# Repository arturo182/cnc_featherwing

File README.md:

# CNC FeatherWing

Inspired by the Arduino CNC Shield, offers similar functionality. 

Requires a Feather-compatible board.

- 4 slots for Pololu stepper motor drivers, 3 axis + 1 clone axis (configurable via jumpers)
- Endstops for X/Y/Z with selectable active level (high or low)
- Pins for external buttons including emergency stop
- Pins for spindle and collant control
- Configurable microstep resolution via jumpers

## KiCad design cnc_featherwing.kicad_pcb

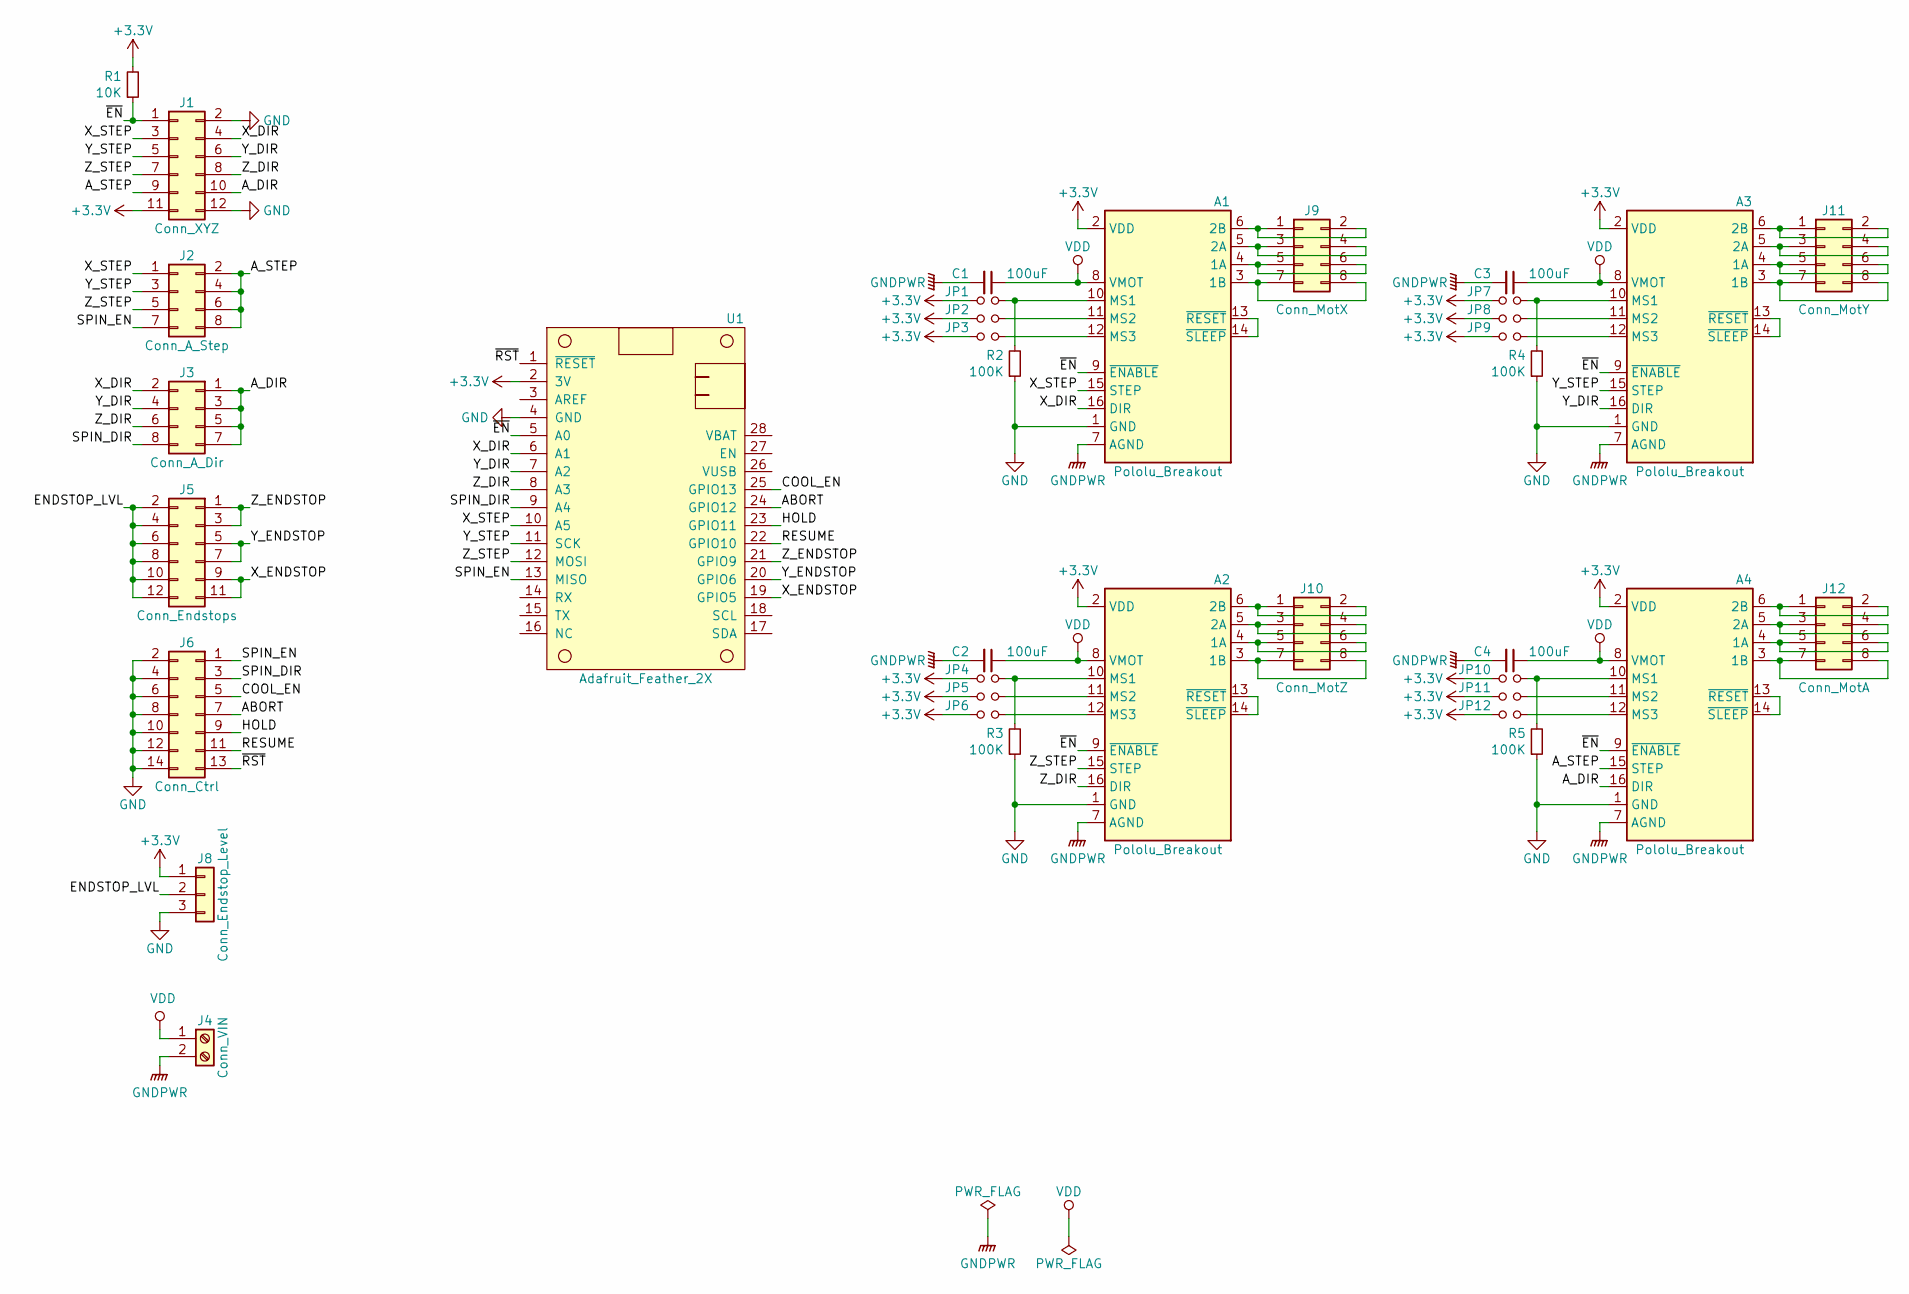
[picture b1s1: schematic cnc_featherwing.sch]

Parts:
A1, A2, A3, A4: Pololu_Breakout; Pololu_Breakout-16_15.2x20.3mm
C1, C2, C3, C4: 100uF; CP_Elec_6.3x7.7
J1: Conn_XYZ; PinHeader_2x06_P2.54mm_Vertical
J2: Conn_A_Step; PinHeader_2x04_P2.54mm_Vertical
J3: Conn_A_Dir; PinHeader_2x04_P2.54mm_Vertical
J4: Conn_VIN; TerminalBlock_bornier-2_P5.08mm
J5: Conn_Endstops; PinHeader_2x06_P2.54mm_Vertical
J6: Conn_Ctrl; PinHeader_2x07_P2.54mm_Vertical
J8: Conn_Endstop_Level; PinHeader_1x03_P2.54mm_Vertical
J9: Conn_MotX; PinHeader_2x04_P2.54mm_Vertical
J10: Conn_MotZ; PinHeader_2x04_P2.54mm_Vertical
J11: Conn_MotY; PinHeader_2x04_P2.54mm_Vertical
J12: Conn_MotA; PinHeader_2x04_P2.54mm_Vertical
JP1, JP4, JP7, JP10: Jumper_MS1; PinHeader_1x02_P2.54mm_Vertical
JP2, JP5, JP8, JP11: Jumper_MS2; PinHeader_1x02_P2.54mm_Vertical
JP3, JP6, JP9, JP12: Jumper_MS3; PinHeader_1x02_P2.54mm_Vertical
R1: 10K; R_0603_1608Metric
R2, R3, R4, R5: 100K; R_0603_1608Metric
U1: Adafruit_Feather_2X; FeatherWing

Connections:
+3V3: A1.2 (VDD), A2.2 (VDD), A3.2 (VDD), A4.2 (VDD), J1.11, J8.1, JP1.1, JP2.1, JP3.1, JP4.1, JP5.1, JP6.1, JP7.1, JP8.1, JP9.1, JP10.1, JP11.1, JP12.1, R1.2, U1.2 (3V)
/ABORT: J6.7, U1.24 (GPIO12)
/A_DIR: A4.16 (DIR), J1.10, J3.1, J3.3, J3.5, J3.7
/A_STEP: A4.15 (STEP), J1.9, J2.2, J2.4, J2.6, J2.8
/COOL_EN: J6.5, U1.25 (GPIO13)
/ENDSTOP_LVL: J5.2, J5.4, J5.6, J5.8, J5.10, J5.12, J8.2
/HOLD: J6.9, U1.23 (GPIO11)
/RESUME: J6.11, U1.22 (GPIO10)
/SPIN_DIR: J3.8, J6.3, U1.9 (A4)
/SPIN_EN: J2.7, J6.1, U1.13 (MISO)
/X_DIR: A1.16 (DIR), J1.4, J3.2, U1.6 (A1)
/X_ENDSTOP: J5.9, J5.11, U1.19 (GPIO5)
/X_STEP: A1.15 (STEP), J1.3, J2.1, U1.10 (A5)
/Y_DIR: A3.16 (DIR), J1.6, J3.4, U1.7 (A2)
/Y_ENDSTOP: J5.5, J5.7, U1.20 (GPIO6)
/Y_STEP: A3.15 (STEP), J1.5, J2.3, U1.11 (SCK)
/Z_DIR: A2.16 (DIR), J1.8, J3.6, U1.8 (A3)
/Z_ENDSTOP: J5.1, J5.3, U1.21 (GPIO9)
/Z_STEP: A2.15 (STEP), J1.7, J2.5, U1.12 (MOSI)
/~EN~: A1.9 (~ENABLE), A2.9 (~ENABLE), A3.9 (~ENABLE), A4.9 (~ENABLE), J1.1, R1.1, U1.5 (A0)
/~RST~: J6.13, U1.1 (~RESET~)
GND: A1.1 (GND), A2.1 (GND), A3.1 (GND), A4.1 (GND), J1.2, J1.12, J6.2, J6.4, J6.6, J6.8, J6.10, J6.12, J6.14, J8.3, R2.1, R3.1, R4.1, R5.1, U1.4 (GND)
GNDPWR: A1.7 (AGND), A2.7 (AGND), A3.7 (AGND), A4.7 (AGND), C1.2, C2.2, C3.2, C4.2, J4.2
unnamed: A1.3 (1B), J9.7, J9.8
unnamed: A1.4 (1A), J9.5, J9.6
unnamed: A1.5 (2A), J9.3, J9.4
unnamed: A1.6 (2B), J9.1, J9.2
unnamed: A1.10 (MS1), JP1.2, R2.2
unnamed: A1.11 (MS2), JP2.2
unnamed: A1.12 (MS3), JP3.2
unnamed: A1.13 (~RESET), A1.14 (~SLEEP)
unnamed: A2.3 (1B), J10.7, J10.8
unnamed: A2.4 (1A), J10.5, J10.6
unnamed: A2.5 (2A), J10.3, J10.4
unnamed: A2.6 (2B), J10.1, J10.2
unnamed: A2.10 (MS1), JP4.2, R3.2
unnamed: A2.11 (MS2), JP5.2
unnamed: A2.12 (MS3), JP6.2
unnamed: A2.13 (~RESET), A2.14 (~SLEEP)
unnamed: A3.3 (1B), J11.7, J11.8
unnamed: A3.4 (1A), J11.5, J11.6
unnamed: A3.5 (2A), J11.3, J11.4
unnamed: A3.6 (2B), J11.1, J11.2
unnamed: A3.10 (MS1), JP7.2, R4.2
unnamed: A3.11 (MS2), JP8.2
unnamed: A3.12 (MS3), JP9.2
unnamed: A3.13 (~RESET), A3.14 (~SLEEP)
unnamed: A4.3 (1B), J12.7, J12.8
unnamed: A4.4 (1A), J12.5, J12.6
unnamed: A4.5 (2A), J12.3, J12.4
unnamed: A4.6 (2B), J12.1, J12.2
unnamed: A4.10 (MS1), JP10.2, R5.2
unnamed: A4.11 (MS2), JP11.2
unnamed: A4.12 (MS3), JP12.2
unnamed: A4.13 (~RESET), A4.14 (~SLEEP)
VDD: A1.8 (VMOT), A2.8 (VMOT), A3.8 (VMOT), A4.8 (VMOT), C1.1, C2.1, C3.1, C4.1, J4.1

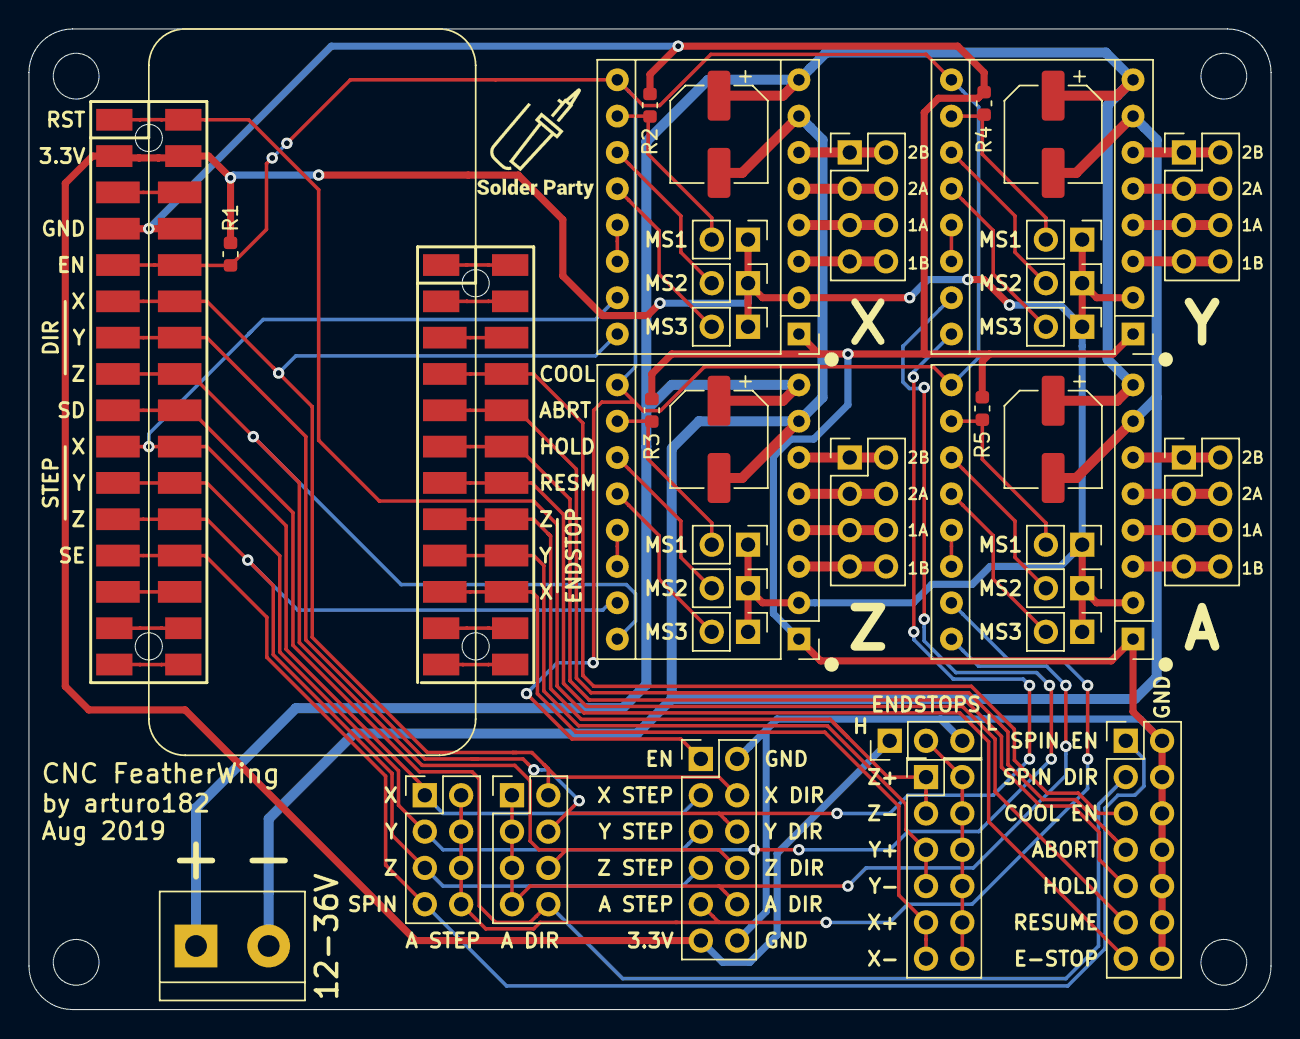
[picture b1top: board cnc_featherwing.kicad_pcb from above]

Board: 2 copper layers, 86.9 x 68.6 mm, 37 parts (0 on the bottom side), 56 nets.

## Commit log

2019-08-11 Initial import
2019-08-13 Add schematics
